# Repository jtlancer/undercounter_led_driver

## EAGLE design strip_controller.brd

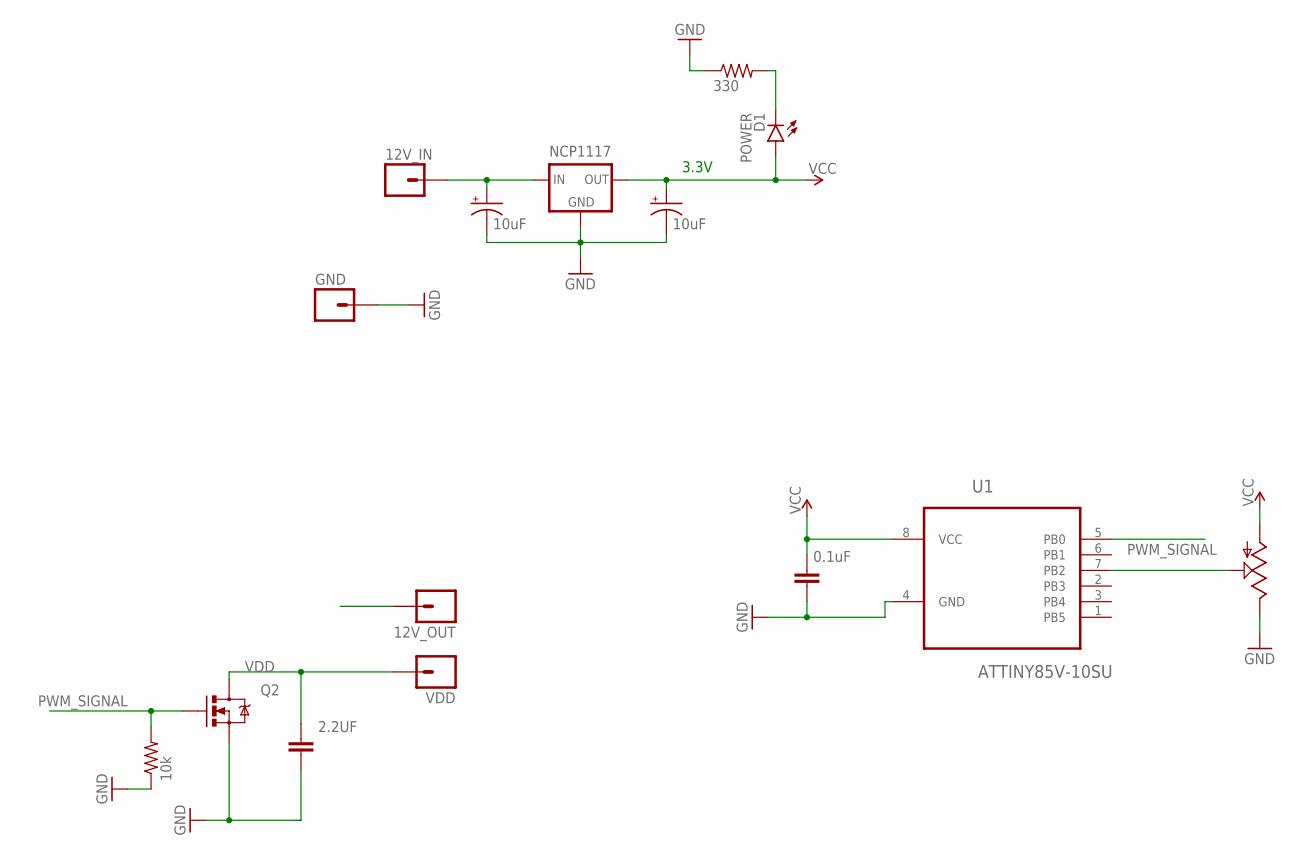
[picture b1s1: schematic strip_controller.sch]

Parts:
12V_IN, 12V_OUT: WAGO_2060M01; WAGO_2060
C2: 0.1uF; 0805
C4: 2.2UF; 1206
C5, C7: 10uF; CAP-PANASONIC-C
D1: POWER; LED-0603
GND: WAGO_2060M01; WAGO_2060
NCP1117: VREG-3.3VNCP1117; TO-252
Q2: MOSFET-NCHANNELFDD8780; DPAK
U1: ATTINY85V-10SU; SOIC127P798X216-8N
U$2: BOURNS_SLIDE_POT; BOURN_SLIDE_POT
U$3: 330; RESISTOR-0805
U$15: 10k; RESISTOR-0805
VDD: WAGO_2060M01; WAGO_2060

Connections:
3.3V: C2.1, C7.+, D1.A, NCP1117.2 (OUT), U1.8 (VCC), U$2.P$6 (1)
12V: 12V_IN.L1.2, 12V_OUT.L1.2, C5.+, NCP1117.3 (IN)
GND: C2.2, C4.1, C5.-, C7.-, GND.L1.2, NCP1117.1 (GND), Q2.3 (S), U1.4 (GND), U$2.P$7 (3), U$3.1, U$15.1
unnamed: D1.C, U$3.2
PWM_SIGNAL: Q2.1 (G), U1.5 (PB0), U$15.2
VDD: C4.2, Q2.4 (D), VDD.L1.2
WIPER: U1.7 (PB2), U$2.P$5 (2)

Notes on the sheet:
3.3V

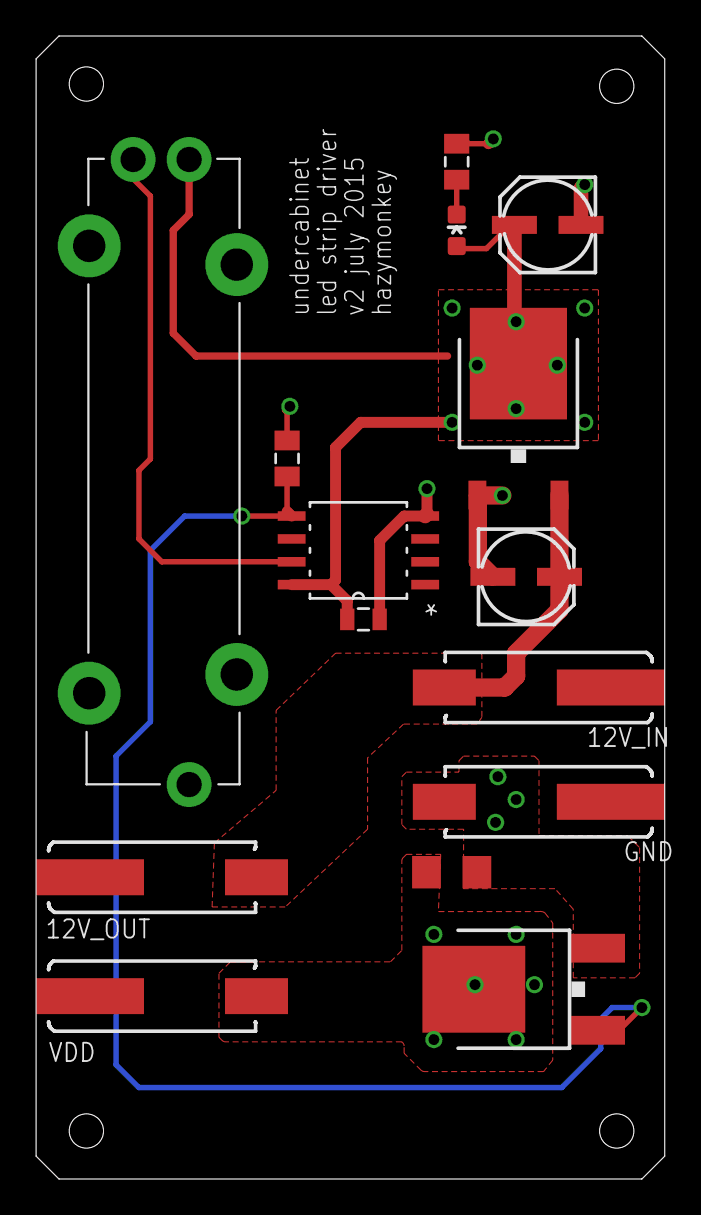
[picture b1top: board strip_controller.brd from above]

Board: 2 copper layers, 34.9 x 63.5 mm, 15 parts (0 on the bottom side), 7 nets.

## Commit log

2015-07-11 version 2 board uploaded to oshpark on 7-11-15

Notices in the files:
parts and their libraries:
SparkFun-Capacitors: Licensing: CC v3.0 Share-Alike You are welcome to use this library for commercial purposes.
SparkFun-DiscreteSemi: Licensing: Creative Commons ShareAlike 4.0 International - https://creativecommons.org/licenses/by-sa/4.0
